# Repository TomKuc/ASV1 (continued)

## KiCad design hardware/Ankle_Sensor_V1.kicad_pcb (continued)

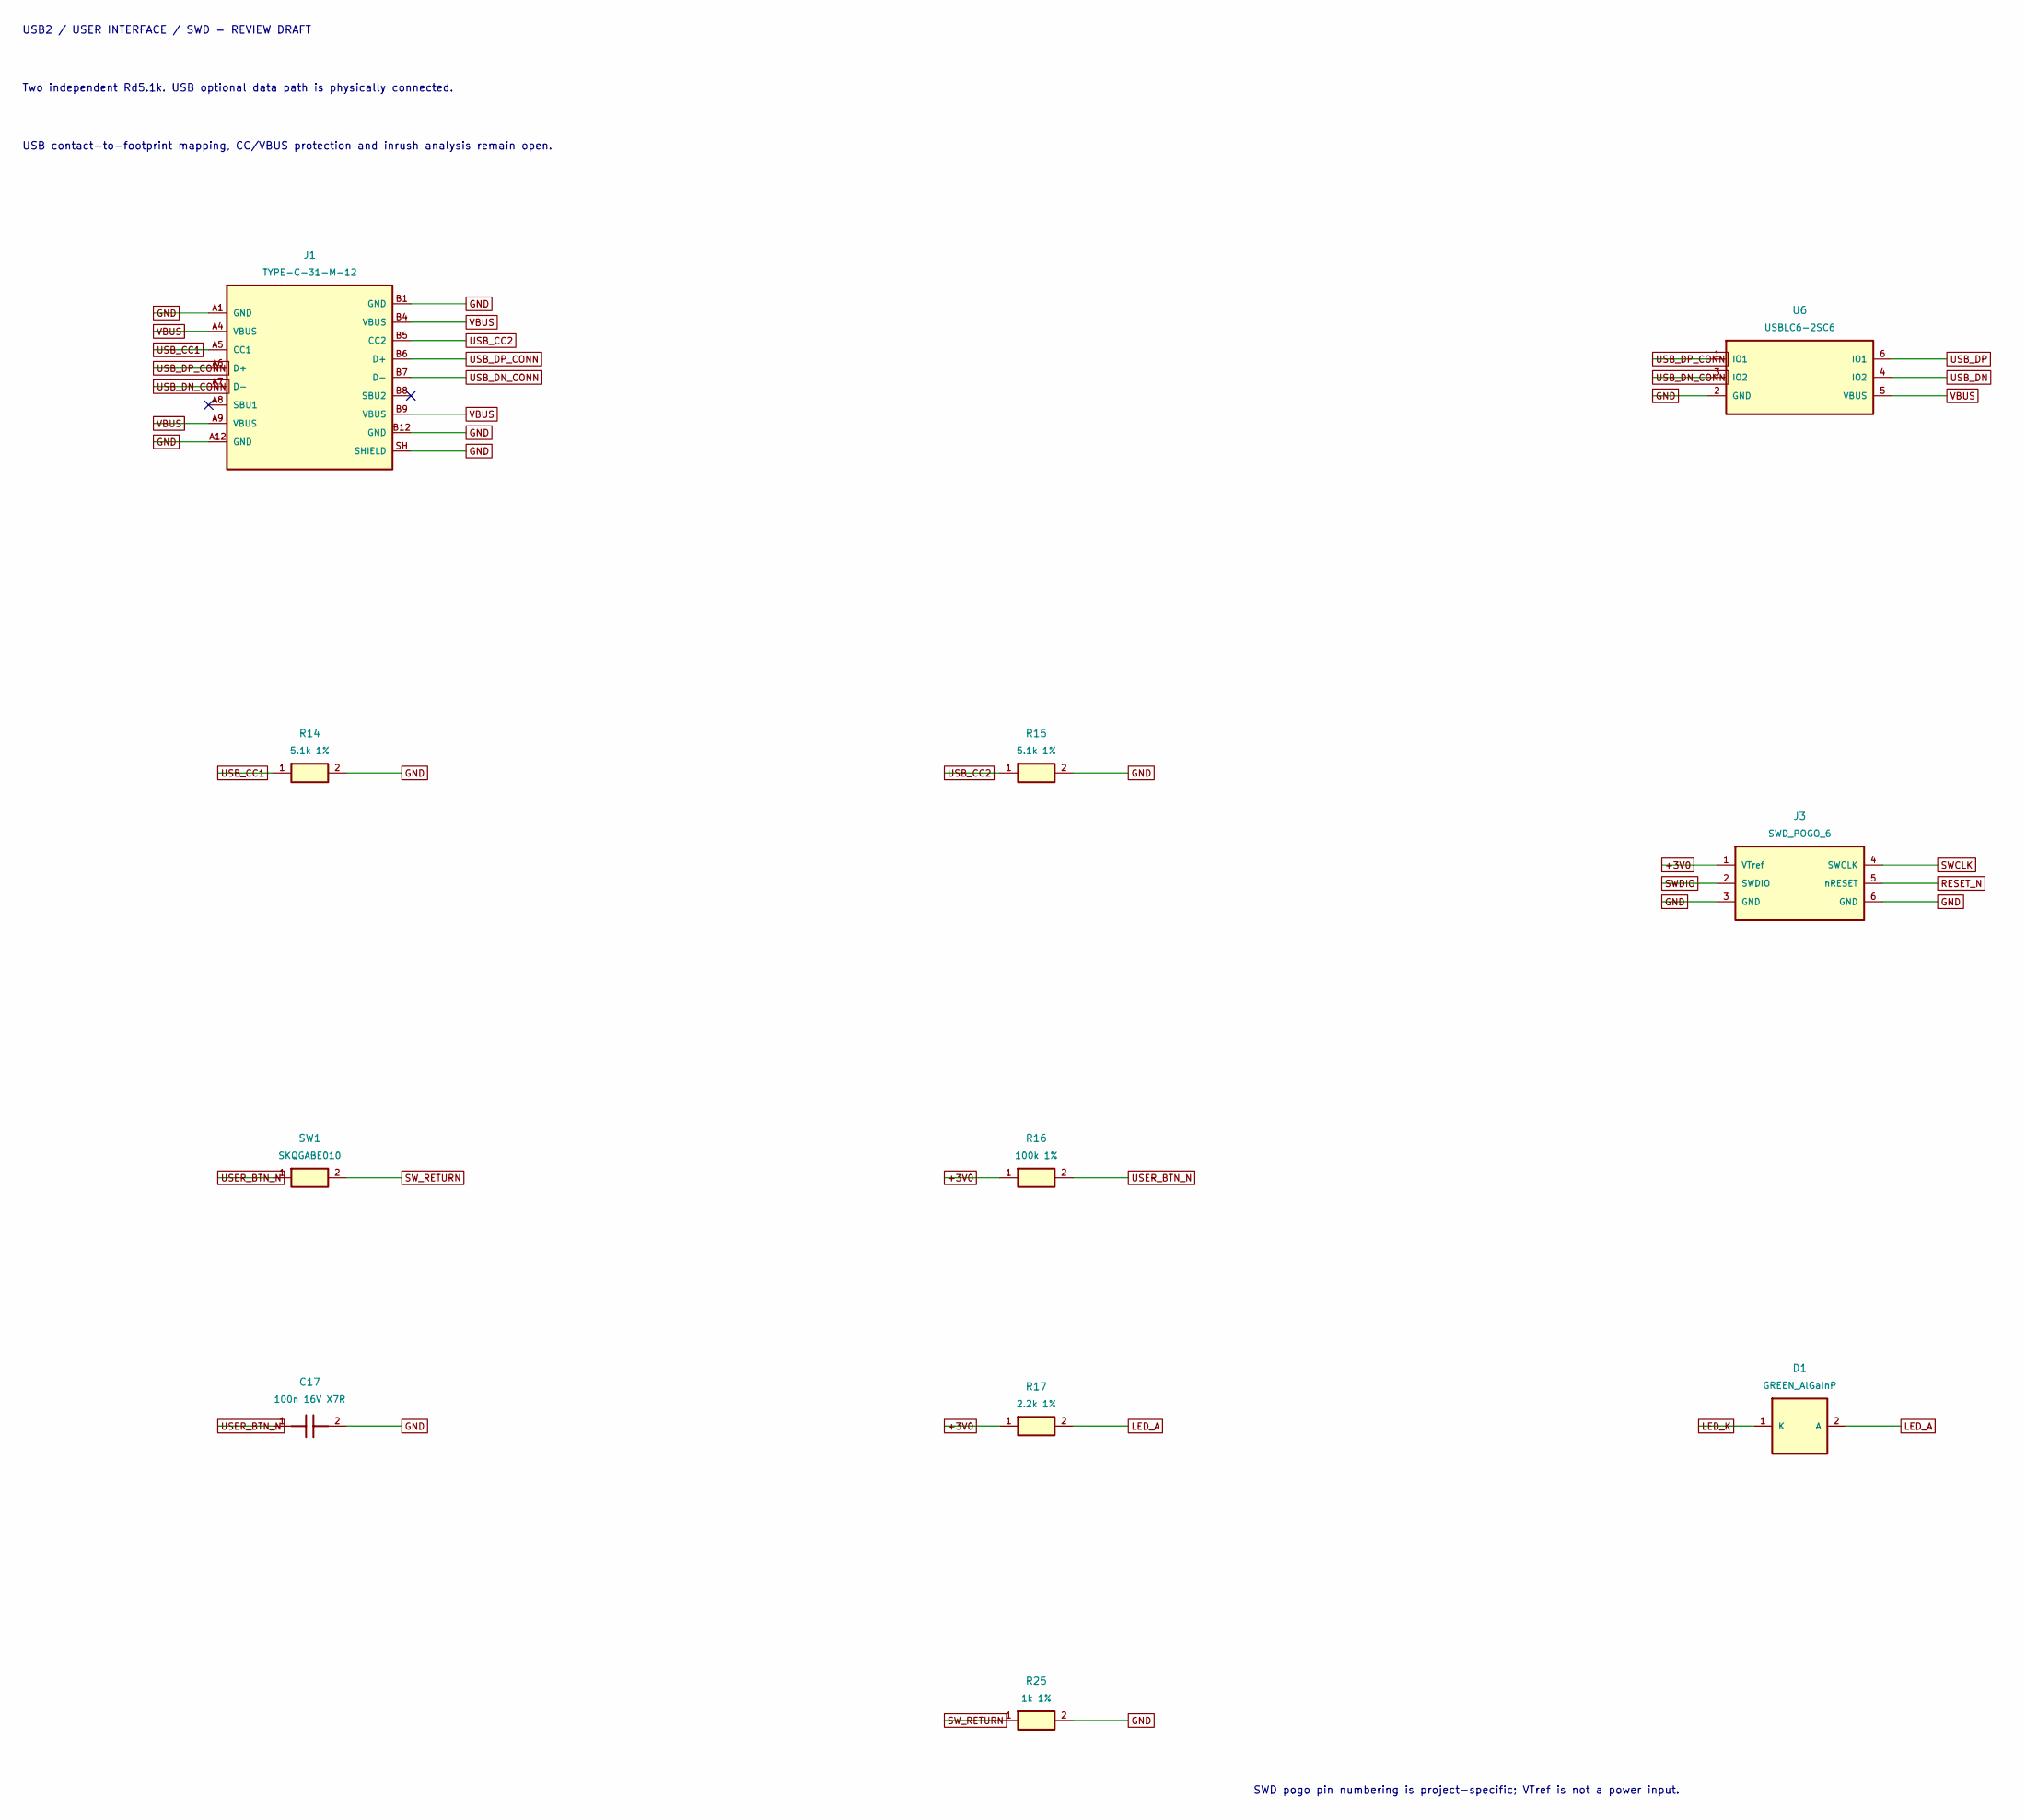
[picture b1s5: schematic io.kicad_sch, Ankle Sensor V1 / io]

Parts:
C17: 100n 16V X7R; C_0402_1005Metric; MPN CL05B104KO5NNNC; JLCPCB C1525
D1: GREEN_AlGaInP; LED_0603_1608Metric; MPN 19-217/G7C-AN1P2/6T; JLCPCB C2986030
J1: TYPE-C-31-M-12; USB_C_Receptacle_HRO_TYPE-C-31-M-12; MPN TYPE-C-31-M-12; JLCPCB C165948
J3: SWD_POGO_6; SWD_Pogo_2x03_P2.54mm
R14, R15: 5.1k 1%; R_0402_1005Metric; MPN 0402WGF5101TCE; JLCPCB C25905
R16: 100k 1%; R_0402_1005Metric; MPN 0402WGF1003TCE; JLCPCB C25741
R17: 2.2k 1%; R_0402_1005Metric; MPN 0402WGF2201TCE; JLCPCB C25879
R25: 1k 1%; R_0402_1005Metric; MPN 0402WGF1001TCE; JLCPCB C11702
SW1: SKQGABE010; SW_SPST_SKQG_WithStem; MPN SKQGABE010; JLCPCB C115351
U6: USBLC6-2SC6; SOT-23-6; MPN USBLC6-2SC6; JLCPCB C7519

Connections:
+3V0: J3.1 (VTref), R16.1, R17.1; also elsewhere on the board
GND: C17.2, J1.A1 (GND), J1.A12 (GND), J1.B1 (GND), J1.B12 (GND), J1.SH (SHIELD), J3.3 (GND), J3.6 (GND), R14.2, R15.2, R25.2, U6.2 (GND); also elsewhere on the board
LED_A: D1.2 (A), R17.2
LED_K: D1.1 (K); also elsewhere on the board
RESET_N: J3.5 (nRESET); also elsewhere on the board
SWCLK: J3.4 (SWCLK); also elsewhere on the board
SWDIO: J3.2 (SWDIO); also elsewhere on the board
SW_RETURN: R25.1, SW1.2
USB_CC1: J1.A5 (CC1), R14.1
USB_CC2: J1.B5 (CC2), R15.1
USB_DN: U6.4 (IO2); also elsewhere on the board
USB_DN_CONN: J1.A7 (D-), J1.B7 (D-), U6.3 (IO2)
USB_DP: U6.6 (IO1); also elsewhere on the board
USB_DP_CONN: J1.A6 (D+), J1.B6 (D+), U6.1 (IO1)
USER_BTN_N: C17.1, R16.2, SW1.1; also elsewhere on the board
VBUS: J1.A4 (VBUS), J1.A9 (VBUS), J1.B4 (VBUS), J1.B9 (VBUS), U6.5 (VBUS); also elsewhere on the board

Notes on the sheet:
USB2 / USER INTERFACE / SWD - REVIEW DRAFT
Two independent Rd5.1k. USB optional data path is physically connected.
USB contact-to-footprint mapping, CC/VBUS protection and inrush analysis remain open.
SWD pogo pin numbering is project-specific; VTref is not a power input.

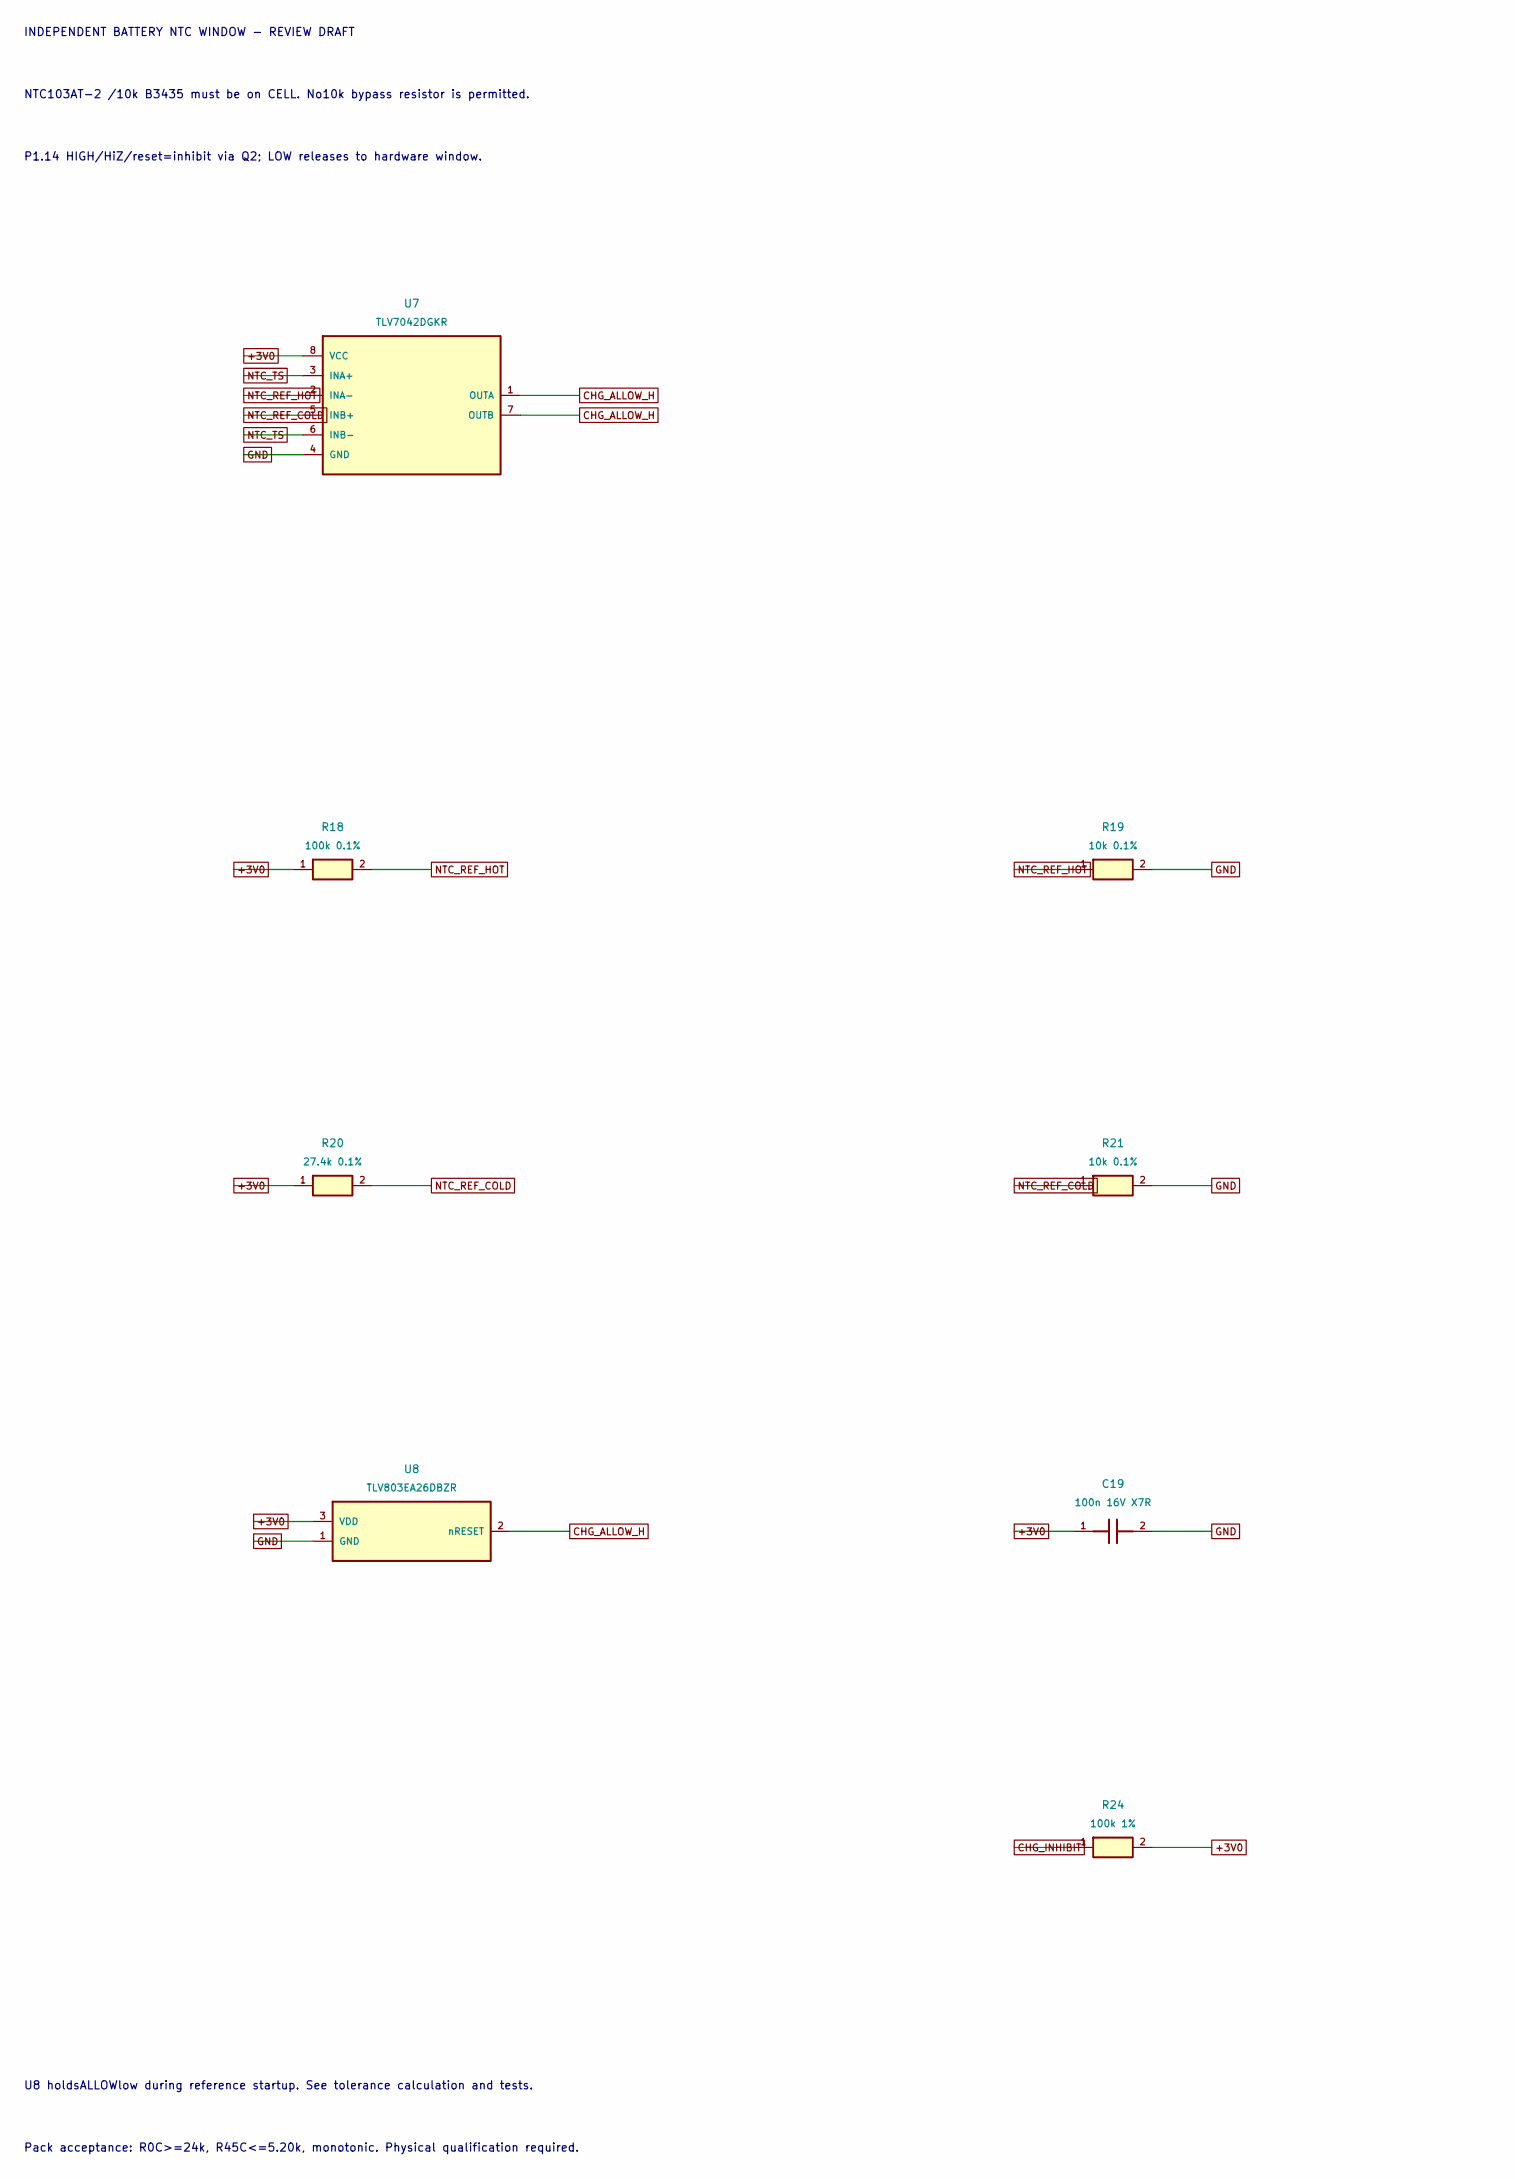
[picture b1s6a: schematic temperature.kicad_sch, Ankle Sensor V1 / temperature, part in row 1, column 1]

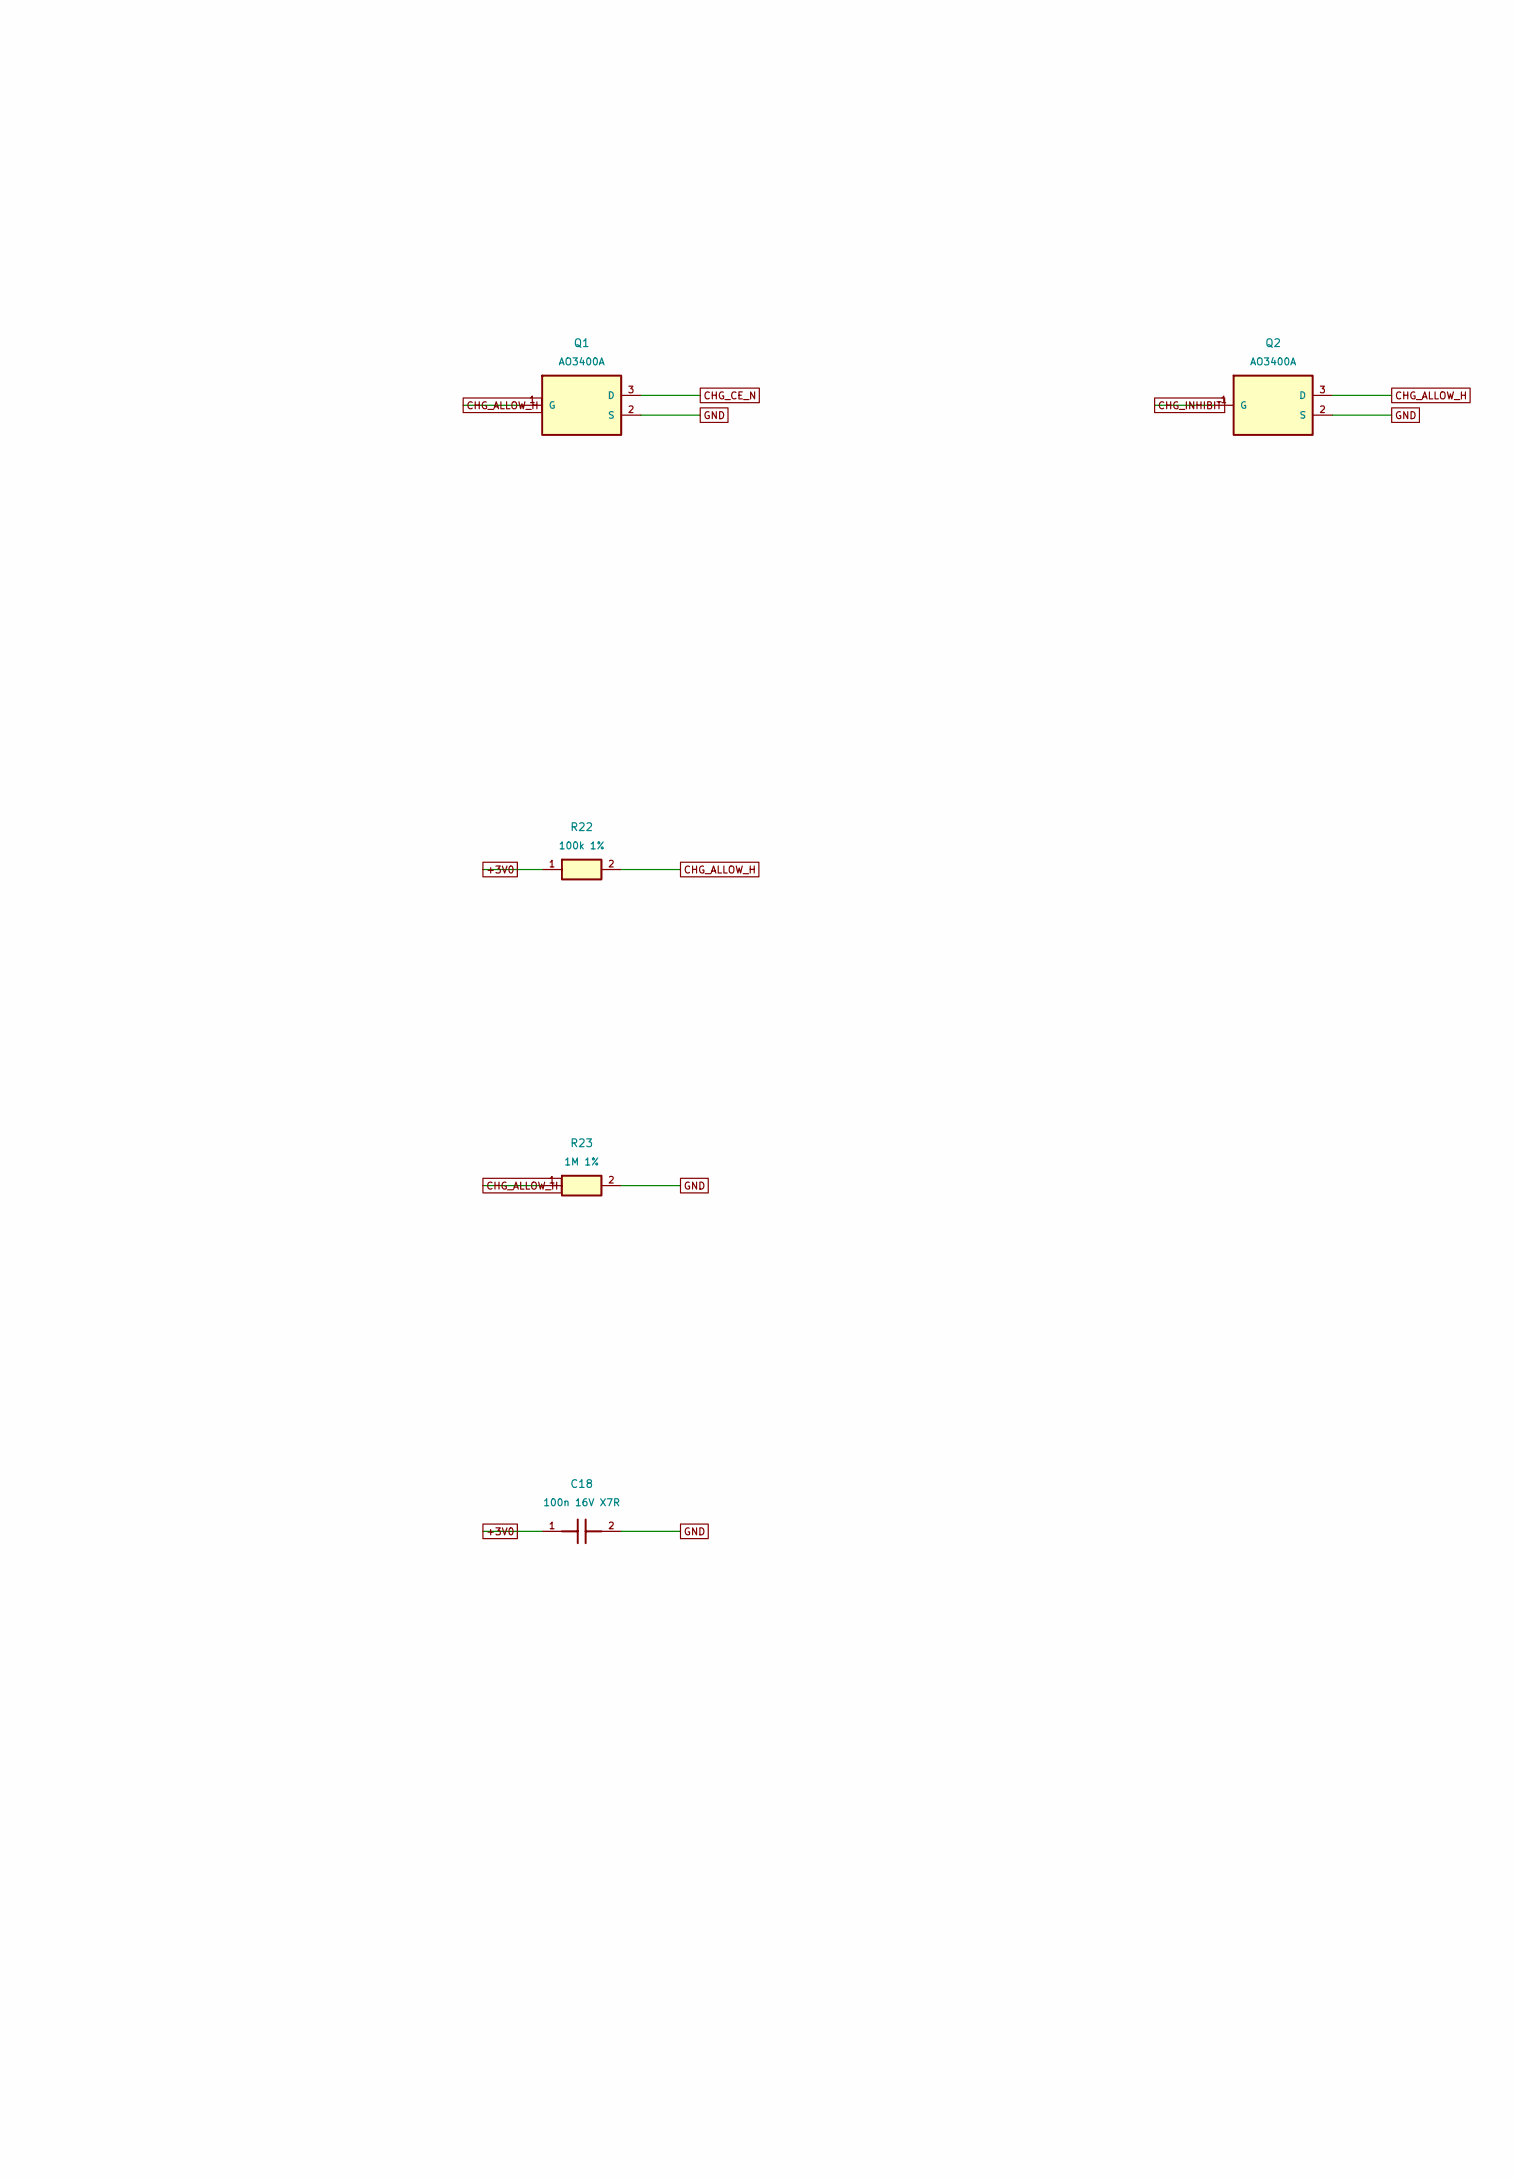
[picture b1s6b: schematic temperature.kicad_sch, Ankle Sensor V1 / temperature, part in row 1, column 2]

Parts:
C18, C19: 100n 16V X7R; C_0402_1005Metric; MPN CL05B104KO5NNNC; JLCPCB C1525
Q1, Q2: AO3400A; SOT-23; MPN AO3400A; JLCPCB C20917
R18: 100k 0.1%; R_0402_1005Metric; MPN ERA2AEB104X; JLCPCB C445619
R19, R21: 10k 0.1%; R_0402_1005Metric; MPN RT0402BRD0710KL; JLCPCB C190095
R20: 27.4k 0.1%; R_0402_1005Metric; MPN RT0402BRD0727K4L; JLCPCB C852679
R22, R24: 100k 1%; R_0402_1005Metric; MPN 0402WGF1003TCE; JLCPCB C25741
R23: 1M 1%; R_0402_1005Metric; MPN 0402WGF1004TCE; JLCPCB C26083
U7: TLV7042DGKR; VSSOP-8_3x3mm_P0.65mm; MPN TLV7042DGKR; JLCPCB C2760466
U8: TLV803EA26DBZR; SOT-23; MPN TLV803EA26DBZR; JLCPCB C1852119

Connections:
+3V0: C18.1, C19.1, R18.1, R20.1, R22.1, R24.2, U7.8 (VCC), U8.3 (VDD); also elsewhere on the board
CHG_ALLOW_H: Q1.1 (G), Q2.3 (D), R22.2, R23.1, U7.1 (OUTA), U7.7 (OUTB), U8.2 (nRESET); also elsewhere on the board
CHG_CE_N: Q1.3 (D); also elsewhere on the board
CHG_INHIBIT: Q2.1 (G), R24.1; also elsewhere on the board
GND: C18.2, C19.2, Q1.2 (S), Q2.2 (S), R19.2, R21.2, R23.2, U7.4 (GND), U8.1 (GND); also elsewhere on the board
NTC_REF_COLD: R20.2, R21.1, U7.5 (INB+)
NTC_REF_HOT: R18.2, R19.1, U7.2 (INA-)
NTC_TS: U7.3 (INA+), U7.6 (INB-); also elsewhere on the board

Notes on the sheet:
INDEPENDENT BATTERY NTC WINDOW - REVIEW DRAFT
NTC103AT-2 /10k B3435 must be on CELL. No10k bypass resistor is permitted.
P1.14 HIGH/HiZ/reset=inhibit via Q2; LOW releases to hardware window.
U8 holdsALLOWlow during reference startup. See tolerance calculation and tests.
Pack acceptance: R0C>=24k, R45C<=5.20k, monotonic. Physical qualification required.

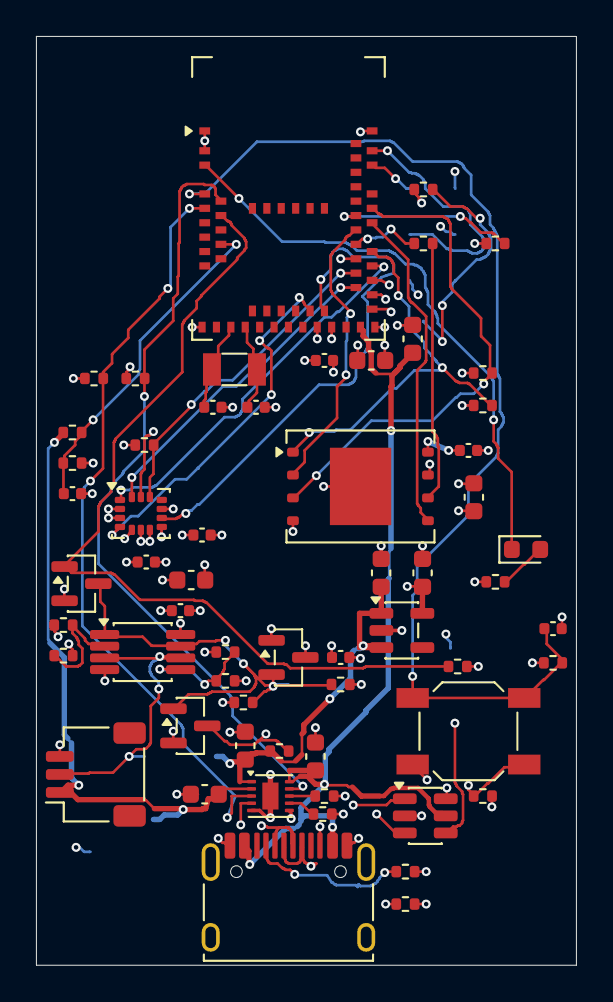
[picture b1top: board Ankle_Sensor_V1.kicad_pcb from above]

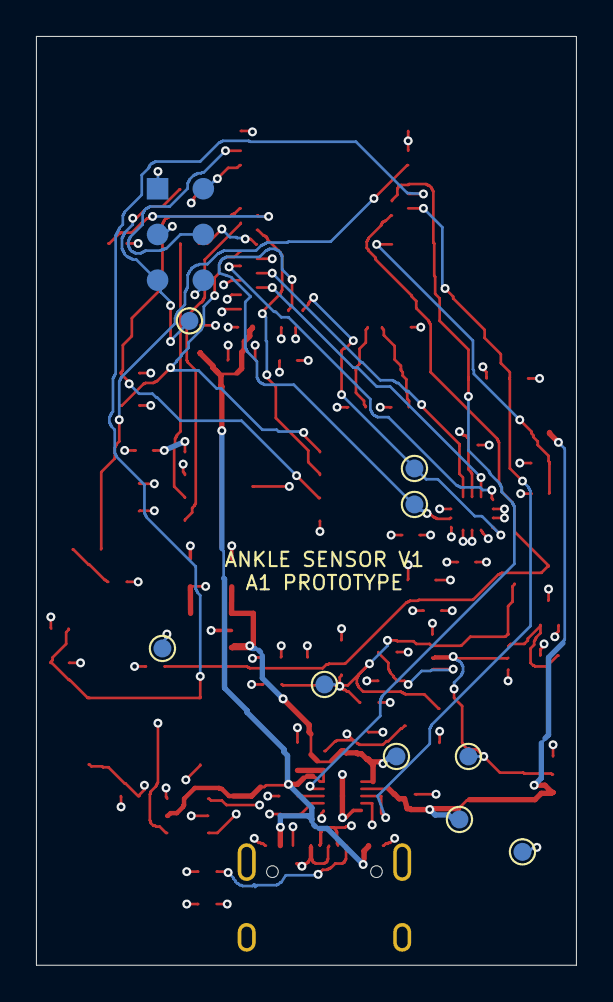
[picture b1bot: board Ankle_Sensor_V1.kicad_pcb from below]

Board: 4 copper layers, 30.0 x 51.6 mm, 69 parts (10 on the bottom side), 44 nets.

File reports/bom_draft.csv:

ref,value,mpn,jlcpcb,footprint,status,note
U1,BQ25185DLHR,BQ25185DLHR,C19725033,AnkleSensor:BQ25185DLHR_DLH0010A_TILandPattern,REVIEW,Independent TLV7042 NTC window controls CE; qualify actual battery and startup
U2,TPS7A2030PDBVR,TPS7A2030PDBVR,C963429,AnkleSensor:SOT-23-5,REVIEW,
J2,JST_SH_3P_PACK_NTC,SM03B-SRSS-TB(LF)(SN),C160403,AnkleSensor:JST_SH_SM03B-SRSS-TB_1x03-1MP_P1.00mm_Horizontal,LCSC_ONLY_PROCUREMENT_REVIEW,"Project cable:1PACK+,2NTC,3PACK-. Never assume off-the-shelf LiPo cable polarity"
R1,24k 1%,0402WGF2402TCE,C25769,AnkleSensor:R_0402_1005Metric,LCSC_ONLY_PROCUREMENT_REVIEW,BQ25185: 4.2V / 100mA input limit
R2,2k 1%,RC0402FR-072KL,C60488,AnkleSensor:R_0402_1005Metric,REVIEW,150mA programmed; actual current constrained by 100mA input and load
R3,100k 1%,0402WGF1003TCE,C25741,AnkleSensor:R_0402_1005Metric,REVIEW,CE defaults HIGH without a valid3V-powered temperature window
R4,10k 1%,0402WGF1002TCE,C25744,AnkleSensor:R_0402_1005Metric,REVIEW,
R5,10k 1%,0402WGF1002TCE,C25744,AnkleSensor:R_0402_1005Metric,REVIEW,
C1,2.2u 25V X5R,CL10A225KA8NNNC,C57895,AnkleSensor:C_0603_1608Metric,REVIEW,Increased from1u to allow tolerance and bias margin; verify Ceff>=1u atVBUSmax5.5V
C2,10u 10V X5R,CL10A106KP8NNNC,C19702,AnkleSensor:C_0603_1608Metric,REVIEW,Ensure effective capacitance >=1uF at4.5V
C3,2.2u 25V X5R,CL10A225KA8NNNC,C57895,AnkleSensor:C_0603_1608Metric,REVIEW,Increased from1u; verify Ceff>=1u at4.2V including temperature/aging
C4,2.2u 16V X5R,CL10A225KO8NNNC,C23630,AnkleSensor:C_0603_1608Metric,REVIEW,Local LDO input; include in effective USB inrush analysis
C5,10u 10V X5R,CL10A106KP8NNNC,C19702,AnkleSensor:C_0603_1608Metric,REVIEW,"LDO local output; validate DC bias, transient and ESR"
R6,1M 1%,0402WGF1004TCE,C26083,AnkleSensor:R_0402_1005Metric,REVIEW,
R7,1M 1%,0402WGF1004TCE,C26083,AnkleSensor:R_0402_1005Metric,REVIEW,
C6,100n 16V X7R,CL05B104KO5NNNC,C1525,AnkleSensor:C_0402_1005Metric,REVIEW,SAADC acquisition >=40us; divider tau50ms
TP1,VSYS,,,AnkleSensor:TestPoint_Pad_D1.0mm,NOT_ASSEMBLED,
TP2,+3V0,,,AnkleSensor:TestPoint_Pad_D1.0mm,NOT_ASSEMBLED,
TP3,VBAT,,,AnkleSensor:TestPoint_Pad_D1.0mm,NOT_ASSEMBLED,
TP4,GND,,,AnkleSensor:TestPoint_Pad_D1.0mm,NOT_ASSEMBLED,
U3,MDBT50Q-P1MV2,MDBT50Q-P1MV2,C5119772,AnkleSensor:Raytac_MDBT50Q,REVIEW,DCCH31 provisionally NC in normal voltage mode; visually verify8.3. Footprint unresolved. P1.14 HIGH inhibits charging throughQ2
Y1,32.768kHz CL7pF,ABS07-32.768KHZ-7-T,C276424,AnkleSensor:Crystal_SMD_3215-2Pin_3.2x1.5mm,REVIEW,JLC catalog verified C276424; CL7pF ESR70k max; land pattern and oscillator qualification pending
C7,10p 50V C0G DRAFT,CL05C100JB5NNNC,C32949,AnkleSensor:C_0402_1005Metric,REVIEW,CL=7pF with assumed2pF stray; tune after parasitic review
C8,10p 50V C0G DRAFT,CL05C100JB5NNNC,C32949,AnkleSensor:C_0402_1005Metric,REVIEW,Provisional load capacitor; not a verified oscillator design
C9,4.7u 10V X5R,CL10A475KP8NNNC,C1705,AnkleSensor:C_0603_1608Metric,REVIEW,
C10,100n 16V X7R,CL05B104KO5NNNC,C1525,AnkleSensor:C_0402_1005Metric,REVIEW,
C11,4.7u 10V X5R,CL10A475KP8NNNC,C1705,AnkleSensor:C_0603_1608Metric,REVIEW,Confirm against Raytac USB reference before release
R8,10k 1%,0402WGF1002TCE,C25744,AnkleSensor:R_0402_1005Metric,REVIEW,
TP5,RESET_N,,,AnkleSensor:TestPoint_Pad_D1.0mm,NOT_ASSEMBLED,
U4,LSM6DSV32XTR,LSM6DSV32XTR,C22461202,AnkleSensor:ST_LSM6DSV32X_LGA14_3x2.5mm_P0.5mm,REVIEW,SDO_Aux11 NC permitted by ST main-SPI mode. Disabled Qvar pins2/3 tiedGND perDS; ERC pin-type warnings reviewed
U5,W25Q01JVZEIQ_128MiB,W25Q01JVZEIQ,C5137036,AnkleSensor:WSON-8-1EP_8x6mm_P1.27mm_EP3.4x4.3mm,REVIEW,128MiB dual-die. Firmware EN4B+per-die BUSY/state handling required. EP/paste geometry review pending
C12,100n 16V X7R,CL05B104KO5NNNC,C1525,AnkleSensor:C_0402_1005Metric,REVIEW,Within few mm of IMU VDD8
C13,100n 16V X7R,CL05B104KO5NNNC,C1525,AnkleSensor:C_0402_1005Metric,REVIEW,Within few mm of IMU VDD_IO5
C14,1u 16V X7R,CC0603KRX7R7BB105,C106248,AnkleSensor:C_0603_1608Metric,REVIEW,
C15,100n 16V X7R,CL05B104KO5NNNC,C1525,AnkleSensor:C_0402_1005Metric,REVIEW,Flash VCC local
C16,4.7u 10V X5R,CL10A475KP8NNNC,C1705,AnkleSensor:C_0603_1608Metric,REVIEW,
R9,100k 1%,0402WGF1003TCE,C25741,AnkleSensor:R_0402_1005Metric,REVIEW,
R10,100k 1%,0402WGF1003TCE,C25741,AnkleSensor:R_0402_1005Metric,REVIEW,
R11,22R 1% DRAFT,0402WGF220JTCE,C25092,AnkleSensor:R_0402_1005Metric,REVIEW,Place at MCU source; tune0-33ohm by measurement
R12,100k 1%,0402WGF1003TCE,C25741,AnkleSensor:R_0402_1005Metric,REVIEW,
R13,100k 1%,0402WGF1003TCE,C25741,AnkleSensor:R_0402_1005Metric,REVIEW,
TP6,IMU_INT1,,,AnkleSensor:TestPoint_Pad_D1.0mm,NOT_ASSEMBLED,
TP7,IMU_INT2,,,AnkleSensor:TestPoint_Pad_D1.0mm,NOT_ASSEMBLED,
J1,TYPE-C-31-M-12,TYPE-C-31-M-12,C165948,AnkleSensor:USB_C_Receptacle_HRO_TYPE-C-31-M-12,REVIEW,Logical contact names; physical combined pads and anchor mapping not yet verified
U6,USBLC6-2SC6,USBLC6-2SC6,C7519,AnkleSensor:SOT-23-6,REVIEW,Flow-through protection: do not join across PCB route bypassing package
R14,5.1k 1%,0402WGF5101TCE,C25905,AnkleSensor:R_0402_1005Metric,REVIEW,
R15,5.1k 1%,0402WGF5101TCE,C25905,AnkleSensor:R_0402_1005Metric,REVIEW,
J3,SWD_POGO_6,,,AnkleSensor:SWD_Pogo_2x03_P2.54mm,REVIEW,Project-specific2x3pogo pinout; no TagConnect compatibility claim. VTref sense only
SW1,SKQGABE010,SKQGABE010,C115351,AnkleSensor:SW_SPST_SKQG_WithStem,REVIEW,"ALPS withstem1.5mm, min10uA; R25 limitsC17 contact discharge"
R16,100k 1%,0402WGF1003TCE,C25741,AnkleSensor:R_0402_1005Metric,REVIEW,
C17,100n 16V X7R,CL05B104KO5NNNC,C1525,AnkleSensor:C_0402_1005Metric,REVIEW,
D1,GREEN_AlGaInP,19-217/G7C-AN1P2/6T,C2986030,AnkleSensor:LED_0603_1608Metric,REVIEW,Everlight lowVf green; R17=2.2k givesabout0.3-0.6mA
R17,2.2k 1%,0402WGF2201TCE,C25879,AnkleSensor:R_0402_1005Metric,REVIEW,
TP8,NTC_TS,,,AnkleSensor:TestPoint_Pad_D1.0mm,NOT_ASSEMBLED,
TP9,CHG_ALLOW_H,,,AnkleSensor:TestPoint_Pad_D1.0mm,NOT_ASSEMBLED,
U7,TLV7042DGKR,TLV7042DGKR,C2760466,AnkleSensor:VSSOP-8_3x3mm_P0.65mm,REVIEW,C number verified atLCSC only; JLC procurement remains open
Q1,AO3400A,AO3400A,C20917,AnkleSensor:SOT-23,REVIEW,
R18,100k 0.1%,ERA2AEB104X,C445619,AnkleSensor:R_0402_1005Metric,REVIEW,Includes supply brownout down to supervisor minimum threshold; do not substitute1%
R19,10k 0.1%,RT0402BRD0710KL,C190095,AnkleSensor:R_0402_1005Metric,REVIEW,
R20,27.4k 0.1%,RT0402BRD0727K4L,C852679,AnkleSensor:R_0402_1005Metric,LCSC_ONLY_PROCUREMENT_REVIEW,
R21,10k 0.1%,RT0402BRD0710KL,C190095,AnkleSensor:R_0402_1005Metric,REVIEW,
R22,100k 1%,0402WGF1003TCE,C25741,AnkleSensor:R_0402_1005Metric,REVIEW,Gate voltage min>2.5V with1Mdown and valid3V; battery-only bias current~30uA
R23,1M 1%,0402WGF1004TCE,C26083,AnkleSensor:R_0402_1005Metric,REVIEW,
C18,100n 16V X7R,CL05B104KO5NNNC,C1525,AnkleSensor:C_0402_1005Metric,REVIEW,Comparator local bypass
U8,TLV803EA26DBZR,TLV803EA26DBZR,C1852119,AnkleSensor:SOT-23,REVIEW,"2.64V supervisor, activeLOW open-drain, nominal200ms delay; check exact suffix/pinout"
Q2,AO3400A,AO3400A,C20917,AnkleSensor:SOT-23,REVIEW,MCU HIGH inhibits; cannot override comparator/supervisorLOW
R24,100k 1%,0402WGF1003TCE,C25741,AnkleSensor:R_0402_1005Metric,REVIEW,Q2 defaultsOFF with GPIOHiZ
C19,100n 16V X7R,CL05B104KO5NNNC,C1525,AnkleSensor:C_0402_1005Metric,REVIEW,Supervisor local bypass
R25,1k 1%,0402WGF1001TCE,C11702,AnkleSensor:R_0402_1005Metric,REVIEW,Limits current from C17 through closed switch; LOW still~30mV
